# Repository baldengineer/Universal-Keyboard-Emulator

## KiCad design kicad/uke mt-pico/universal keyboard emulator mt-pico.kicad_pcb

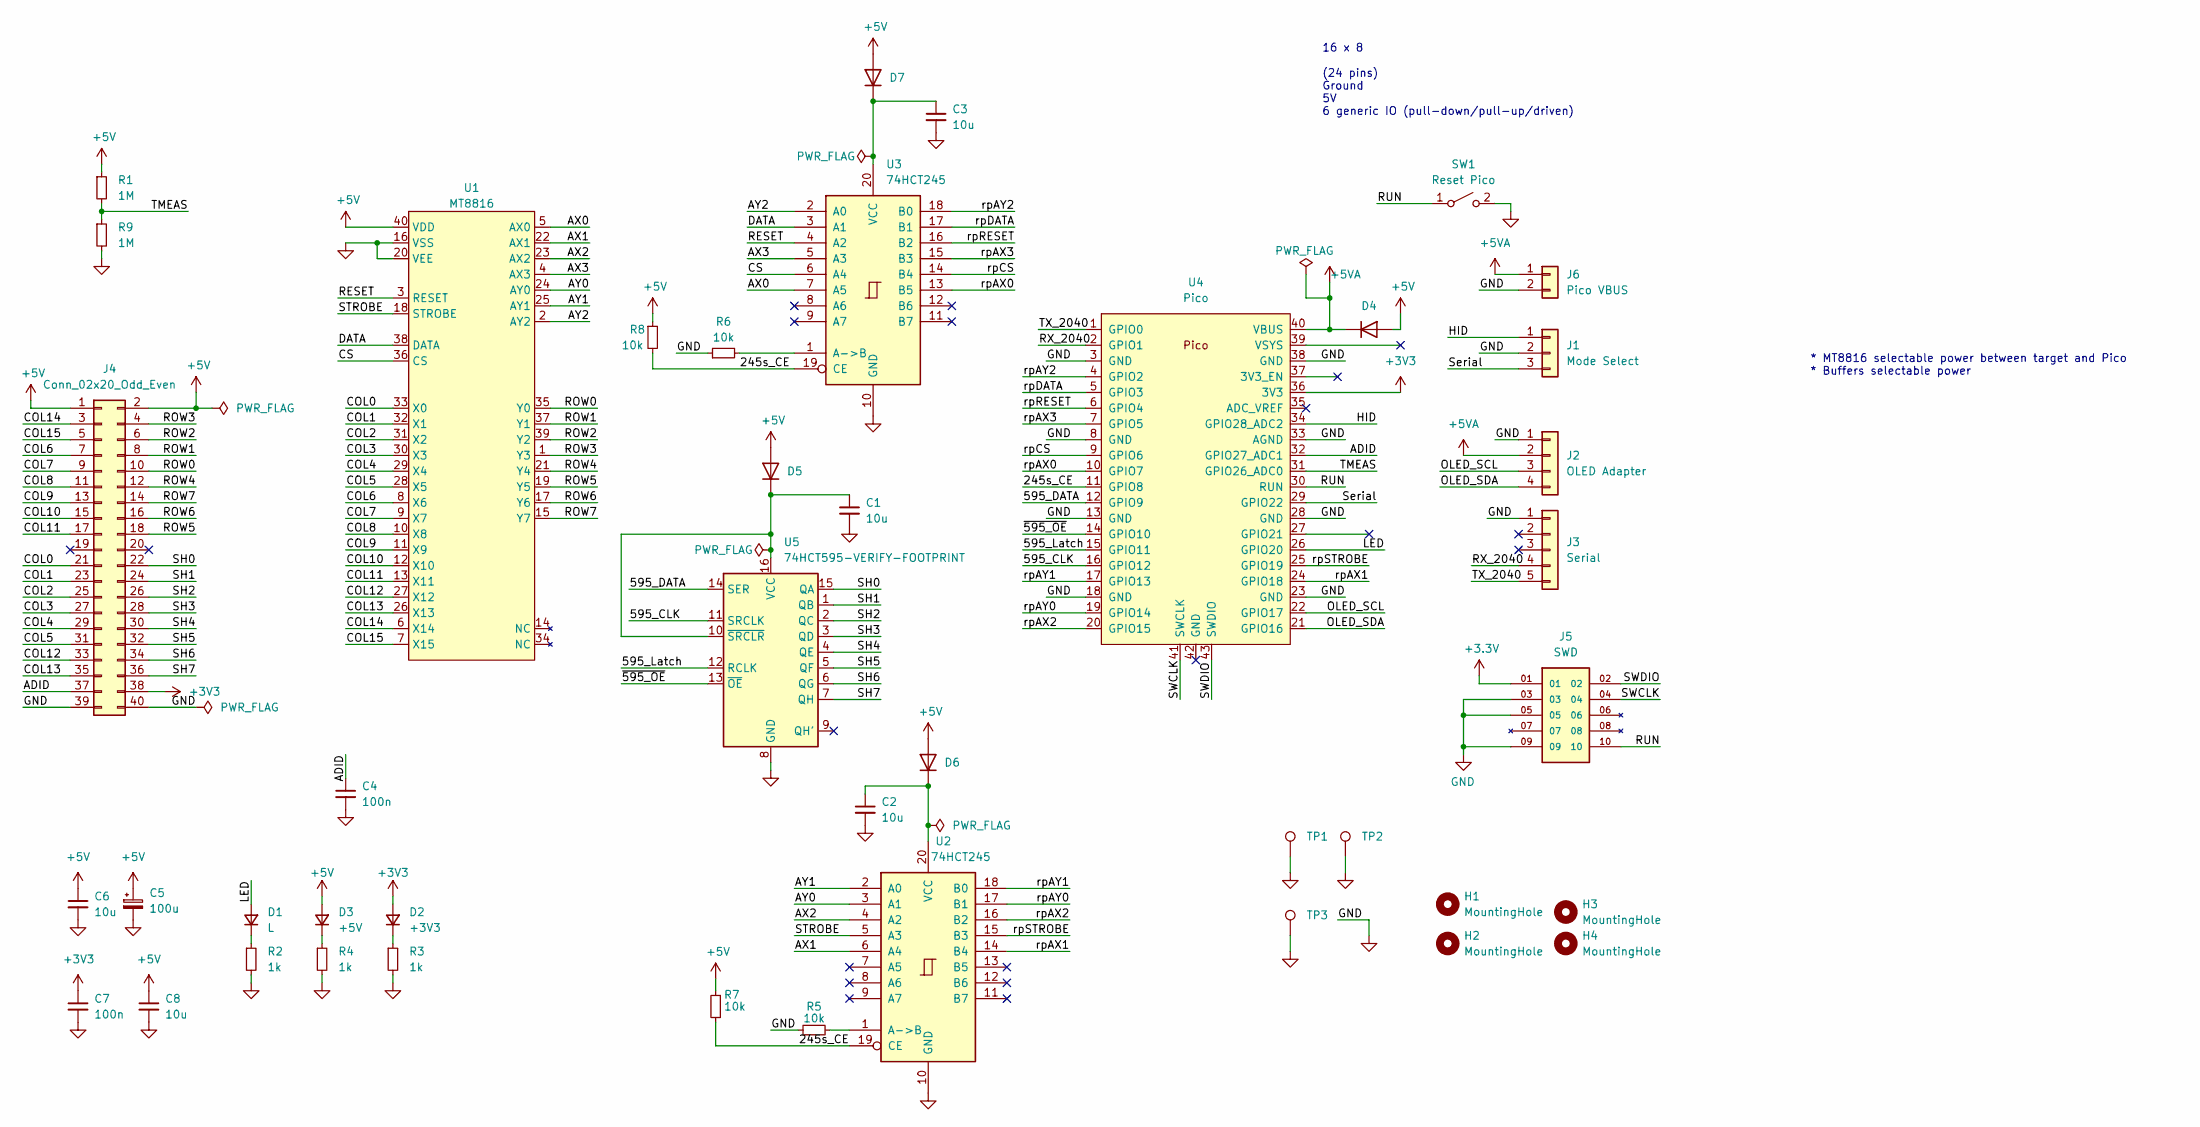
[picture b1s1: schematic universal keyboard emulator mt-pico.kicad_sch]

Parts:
C1, C2, C3, C6, C8: 10u; C_0805_2012Metric
C4, C7: 100n; C_0805_2012Metric
C5: 100u; CP_Radial_D5.0mm_P2.50mm
D1: L; LED_1206_3216Metric
D2: +3V3; LED_1206_3216Metric
D3: +5V; LED_1206_3216Metric
D4: SM4001; D_SMA_Handsoldering
D5, D6, D7: NSVR0320MW2T1G; D_SOD-323_HandSoldering
H1, H2, H3, H4: MountingHole; MountingHole_2.2mm_M2
J1: Mode Select; PinHeader_1x03_P2.54mm_Vertical
J2: OLED Adapter; PinSocket_1x04_P2.54mm_Vertical
J3: Serial; PinHeader_1x05_P2.54mm_Vertical
J4: Conn_02x20_Odd_Even; PinHeader_2x20_P2.54mm_Vertical
J5: SWD; SAMTEC_FTSH-105-XX-X-DV; PARTREV H
J6: Pico VBUS; PinHeader_1x02_P2.54mm_Vertical
R1, R9: 1M; R_0805_2012Metric
R2, R3, R4: 1k; R_0805_2012Metric
R5, R6, R7, R8: 10k; R_0805_2012Metric
SW1: Reset Pico; SW_SPST_PTS810
TP1, TP2, TP3: TestPoint_Harwin; Harwin-S1751-46-Test-Point
U1: MT8816; DIP-40_W15.24mm_Socket_LongPads
U2, U3: 74HCT245; SOIC-20W_7.5x12.8mm_P1.27mm
U4: Pico; RPi_Pico_W_Combined_SMD_TH
U5: 74HCT595-VERIFY-FOOTPRINT; SO-16_3.9x9.9mm_P1.27mm

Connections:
+5V: C5.1, C6.1, C8.1, D3.2 (A), D4.2 (A), D5.2 (A), D6.2 (A), D7.2 (A), J4.1, J4.2, R1.1, R7.1, R8.1, U1.40 (VDD)
+5VA: D4.1 (K), J2.2, J6.1, U4.40 (VBUS)
/245s_CE: R7.2, R8.2, U2.19 (CE), U3.19 (CE), U4.11 (GPIO8)
/595_CLK: U4.16 (GPIO12), U5.11 (SRCLK)
/595_DATA: U4.12 (GPIO9), U5.14 (SER)
/595_Latch: U4.15 (GPIO11), U5.12 (RCLK)
/ADID: C4.1, J4.37, U4.32 (GPIO27_ADC1)
/AX0: U1.5 (AX0), U3.7 (A5)
/AX1: U1.22 (AX1), U2.6 (A4)
/AX2: U1.23 (AX2), U2.4 (A2)
/AX3: U1.4 (AX3), U3.5 (A3)
/AY0: U1.24 (AY0), U2.3 (A1)
/AY1: U1.25 (AY1), U2.2 (A0)
/AY2: U1.2 (AY2), U3.2 (A0)
/COL0: J4.21, U1.33 (X0)
/COL1: J4.23, U1.32 (X1)
/COL2: J4.25, U1.31 (X2)
/COL3: J4.27, U1.30 (X3)
/COL4: J4.29, U1.29 (X4)
/COL5: J4.31, U1.28 (X5)
/COL6: J4.7, U1.8 (X6)
/COL7: J4.9, U1.9 (X7)
/COL8: J4.11, U1.10 (X8)
/COL9: J4.13, U1.11 (X9)
/COL10: J4.15, U1.12 (X10)
/COL11: J4.17, U1.13 (X11)
/COL12: J4.33, U1.27 (X12)
/COL13: J4.35, U1.26 (X13)
/COL14: J4.3, U1.6 (X14)
/COL15: J4.5, U1.7 (X15)
/CS: U1.36 (CS), U3.6 (A4)
/DATA: U1.38 (DATA), U3.3 (A1)
/HID: J1.1, U4.34 (GPIO28_ADC2)
/LED: D1.2 (A), U4.26 (GPIO20)
/OLED_SCL: J2.3, U4.22 (GPIO17)
/OLED_SDA: J2.4, U4.21 (GPIO16)
/RESET: U1.3 (RESET), U3.4 (A2)
/ROW0: J4.10, U1.35 (Y0)
/ROW1: J4.8, U1.37 (Y1)
/ROW2: J4.6, U1.39 (Y2)
/ROW3: J4.4, U1.1 (Y3)
/ROW4: J4.12, U1.21 (Y4)
/ROW5: J4.18, U1.19 (Y5)
/ROW6: J4.16, U1.17 (Y6)
/ROW7: J4.14, U1.15 (Y7)
/RUN: J5.10, SW1.1 (A), U4.30 (RUN)
/RX_2040: J3.4, U4.2 (GPIO1)
/SH0: J4.22, U5.15 (QA)
/SH1: J4.24, U5.1 (QB)
/SH2: J4.26, U5.2 (QC)
/SH3: J4.28, U5.3 (QD)
/SH4: J4.30, U5.4 (QE)
/SH5: J4.32, U5.5 (QF)
/SH6: J4.34, U5.6 (QG)
/SH7: J4.36, U5.7 (QH)
/STROBE: U1.18 (STROBE), U2.5 (A3)
/SWCLK: J5.04, U4.41 (SWCLK)
/SWDIO: J5.02, U4.43 (SWDIO)
/Serial: J1.3, U4.29 (GPIO22)
/TMEAS: R1.2, R9.1, U4.31 (GPIO26_ADC0)
/TX_2040: J3.5, U4.1 (GPIO0)
/rpAX0: U3.13 (B5), U4.10 (GPIO7)
/rpAX1: U2.14 (B4), U4.24 (GPIO18)
/rpAX2: U2.16 (B2), U4.20 (GPIO15)
/rpAX3: U3.15 (B3), U4.7 (GPIO5)
/rpAY0: U2.17 (B1), U4.19 (GPIO14)
/rpAY1: U2.18 (B0), U4.17 (GPIO13)
/rpAY2: U3.18 (B0), U4.4 (GPIO2)
/rpCS: U3.14 (B4), U4.9 (GPIO6)
/rpDATA: U3.17 (B1), U4.5 (GPIO3)
/rpRESET: U3.16 (B2), U4.6 (GPIO4)
/rpSTROBE: U2.15 (B3), U4.25 (GPIO19)
/~595_OE: U4.14 (GPIO10), U5.13 (~OE)
GND: C1.2, C2.2, C3.2, C4.2, C5.2, C6.2, C7.2, C8.2, J1.2, J2.1, J3.1, J4.39, J4.40, J5.03, J5.05, J5.09, J6.2, R2.2, R3.2, R4.2, R5.1, R6.1, R9.2, SW1.2 (B), TP1.1, TP2.1, TP3.1, U1.16 (VSS), U1.20 (VEE), U2.10 (GND), U3.10 (GND), U4.3 (GND), U4.8 (GND), U4.13 (GND), U4.18 (GND), U4.23 (GND), U4.28 (GND), U4.33 (AGND), U4.38 (GND), U5.8 (GND)
unnamed: D1.1 (K), R2.1
unnamed: D2.1 (K), R3.1
unnamed: D3.1 (K), R4.1
unnamed: C1.1, D5.1 (K), U5.10 (~SRCLR), U5.16 (VCC)
unnamed: R5.2, U2.1 (A->B)
unnamed: R6.2, U3.1 (A->B)
unnamed: C2.1, D6.1 (K), U2.20 (VCC)
unnamed: C3.1, D7.1 (K), U3.20 (VCC)

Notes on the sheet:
16 x 8 (24 pins) Ground 5V 6 generic IO (pull-down/pull-up/driven)
* MT8816 selectable power between target and Pico * Buffers selectable power

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
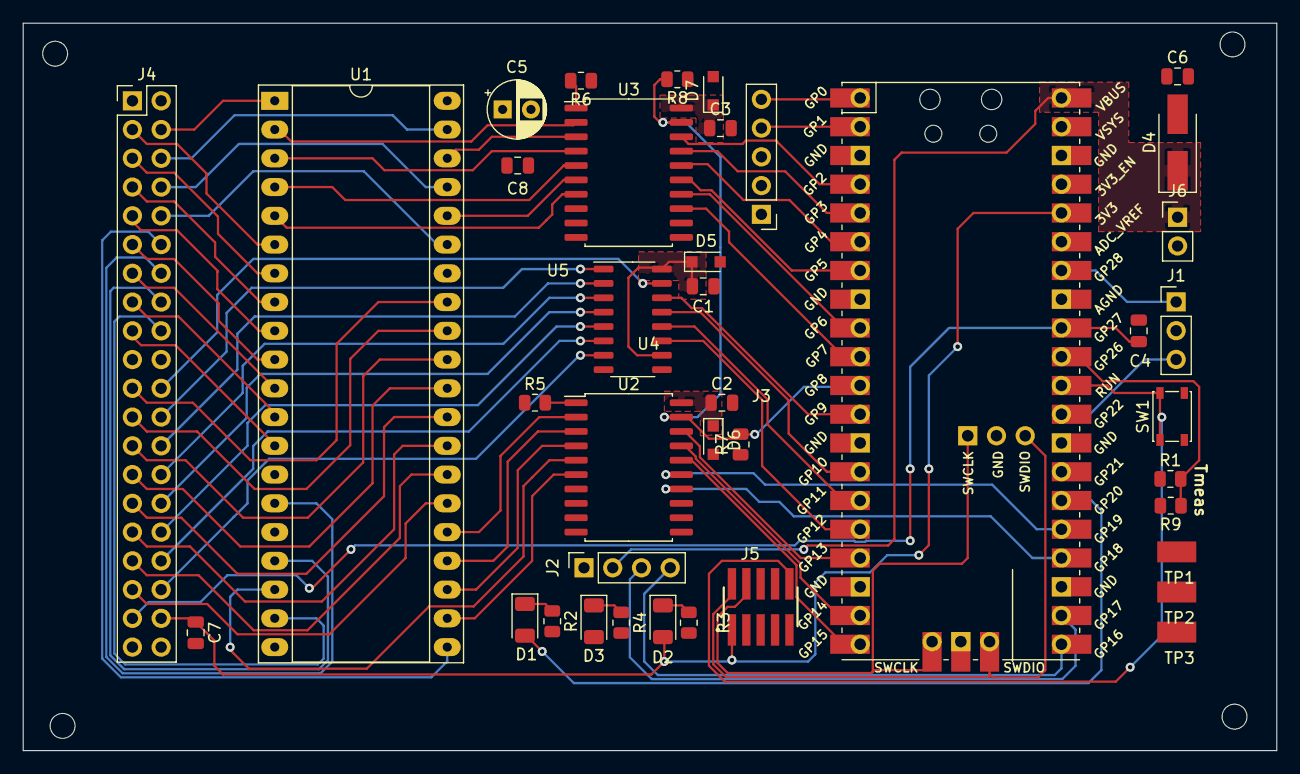
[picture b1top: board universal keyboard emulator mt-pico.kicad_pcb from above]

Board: 2 copper layers, 110.7 x 64.3 mm, 43 parts (0 on the bottom side), 83 nets.

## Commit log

2022-09-19 first pcb floorplan
2022-09-19 removing old backup file
2022-09-20 minor pixel pushing
2022-09-23 Pre-route #1
2022-09-23 all but 5v routed
2022-10-24 final pcb - not yet submitted to fab though
2022-12-19 rough telnet firmware for Pico W with Arduino LIbrary
2022-12-20 wifi config example
2022-12-20 decoding of ctrl-characters, esc codes, and normal keys.
